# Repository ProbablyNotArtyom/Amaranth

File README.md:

https://hackaday.io/project/166535-amaranth-powerpc-homebrew-computer

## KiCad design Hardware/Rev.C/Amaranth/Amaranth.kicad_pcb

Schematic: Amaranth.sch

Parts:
C1, C2, C3, C4, C5, C6, C7, C9, C10, C11, C12, C13: 100nf; C_ARRAY_0612
C15, C16: 10pf; C_0603_1608Metric_Pad1.05x0.95mm_HandSolder
C17, C18, C19, C31, C32, C33: 100uF; CP_Elec_6.3x5.4
C20: 10nf; C_0603_1608Metric_Pad1.05x0.95mm_HandSolder
C21: 100nf; C_0603_1608Metric_Pad1.05x0.95mm_HandSolder
C22: 10uF; CP_EIA-3216-18_Kemet-A_Pad1.58x1.35mm_HandSolder
D1: LED; LED_D5.0mm
H1, H2, H3, H4: MountingHole_Pad; atx_mounting_hole
J1: RJ45_LED; RJ45_Amphenol_RJHSE538X
J2: IDE; IDC-Header_2x20_P2.54mm_Vertical
J3: ATX24; Molex_Mini-Fit_Jr_5566-24A_2x12_P4.20mm_Vertical
J4: KBD; PS2
J5: VGA; Dsub-VGA
L1: L; L_0603_1608Metric_Pad1.05x0.95mm_HandSolder
P1: JTAG; PinHeader_2x10_P2.54mm_Vertical
R1, R16, R21: 10k; R_0805_2012Metric_Pad1.15x1.40mm_HandSolder
R4: 12.4k; R_0603_1608Metric_Pad1.05x0.95mm_HandSolder
R5, R6: 330; R_0603_1608Metric_Pad1.05x0.95mm_HandSolder
R7, R8, R9, R24: 49k9; R_0603_1608Metric_Pad1.05x0.95mm_HandSolder
R10: 330; R_0805_2012Metric_Pad1.15x1.40mm_HandSolder
R11, R12: 2k; R_0805_2012Metric_Pad1.15x1.40mm_HandSolder
R13, R14: 270; R_0805_2012Metric_Pad1.15x1.40mm_HandSolder
R25: 10k; R_1206_3216Metric_Pad1.42x1.75mm_HandSolder
R26: 10k; C_0603_SMALL_REF
R27, R28, R29: 75; C_0603_SMALL_REF
R30, R33: 544; C_0603_SMALL_REF
R31, R34: 1.2k; C_0603_SMALL_REF
R32, R35: 2.4k; C_0603_SMALL_REF
R36: 455; C_0603_SMALL_REF
R37: 986; C_0603_SMALL_REF
RN1, RN2, RN3: 10k; R_ARRAY_BUSSED_8x1206
SW1: SW_SPDT; SW_Lever_1P2T_NKK_GW12LxH
U1: MCF5208; LQFP-160_24x24mm_P0.5mm
U2, U3: AS4C16M16SA; TSSOP-54_6.1x14mm_Pitch0.5mm
U4, U5, U9, U10: IS61WV25616; TSOP-II-44_10.16x18.41mm_P0.8mm
U6, U7, U20: 74LVC16245A; TSSOP-48_6.1x12.5mm_P0.5mm
U12, U14: 10M04SCE144; EQFP-144-1EP_20x20mm_P0.5mm_EP5x5mm
U13: ENC624J600-I_PT; TQFP-64_10x10mm_P0.5mm
U18: SST39SF040; PLCC-32_TH
Y1: 25MHz; Crystal_SMD_HC49-SD
Y2: 100MHz; Oscillator_SMD_EuroQuartz_XO91-4Pin_7.0x5.0mm_HandSoldering

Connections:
8b_L0: U6.48 (1LE), U12.50 (IO3/DIFFIO_TX_RX_B9n/DIFFOUT_B9n)
8b_L1: U6.25 (2LE), U12.52 (IO3/DIFFIO_TX_RX_B9p/DIFFOUT_B9p)
8b_L2: U7.48 (1LE), U12.54 (IO3)
8b_L3: U7.25 (2LE), U12.55 (IO3/DIFFIO_TX_RX_B12n/DIFFOUT_B12n)
8b_OUT: U6.1 (~1OE), U6.24 (~2OE), U7.1 (~1OE), U7.24 (~2OE), U12.56 (IO3/DIFFIO_TX_RX_B12p/DIFFOUT_B12p)
8burst_0: U12.10 (IO1A/DIFFIO_RX_L3p/DIFFOUT_L3p), U18.12 (A0)
8burst_1: U12.11 (IO1A/DIFFIO_RX_L5n/DIFFOUT_L5n), U18.11 (A1)
+1V2: U1.36 (IVDD), U1.74 (IVDD), U1.92 (IVDD), U1.94 (PLL_VDD), U1.121 (IVDD), U1.159 (IVDD)
+3V3: C1.5, C1.6, C1.7, C1.8, C2.5, C2.6, C2.7, C2.8, C3.5, C3.6, C3.7, C3.8, C4.5, C4.6, C4.7, C4.8, C5.5, C5.6, C5.7, C5.8, C6.5, C6.6, C6.7, C6.8, C7.5, C7.6, C7.7, C7.8, C9.5, C9.6, C9.7, C9.8, C10.5, C10.6, C10.7, C10.8, C11.5, C11.6, C11.7, C11.8, C12.5, C12.6, C12.7, C12.8, C13.5, C13.6, C13.7, C13.8, C17.1, C18.1, C19.1, C31.1, C32.1, C33.1, D1.2 (A), J3.1 (3V3), J3.2 (3V3), J3.12 (3V3), J3.13 (3V3), L1.2, R1.1, R16.1, R21.1, RN1.1 (common), RN2.1 (common), RN3.1 (common), U1.2 (EVDD), U1.9 (EVDD), U1.11 (SD_VDD), U1.39 (SD_VDD), U1.41 (SD_VDD), U1.67 (SD_VDD), U1.69 (EVDD), U1.72 (EVDD), U1.80 (EVDD), U1.87 (DRAMSEL), U1.89 (EVDD), U1.95 (EVDD), U1.97 (SD_VDD), U1.118 (SD_VDD), U1.129 (SD_VDD), U1.131 (EVDD), U2.1 (VDD), U2.3 (VDDQ), U2.9 (VDDQ), U2.14 (VDD), U2.27 (VDD), U2.43 (VDDQ), U2.49 (VDDQ), U3.1 (VDD), U3.3 (VDDQ), U3.9 (VDDQ), U3.14 (VDD), U3.27 (VDD), U3.43 (VDDQ), U3.49 (VDDQ), U4.11 (VCC), U4.33 (VCC), U5.11 (VCC), U5.33 (VCC), U6.7 (VCC-1), U6.18 (VCC-2), U6.31 (VCC-3), U6.42 (VCC), U7.7 (VCC-1), U7.18 (VCC-2), U7.31 (VCC-3), U7.42 (VCC), U9.11 (VCC), U9.33 (VCC), U10.11 (VCC), U10.33 (VCC), U12.1 (VCC_ONE), U12.2 (VCCA6), U12.5 (VCCA3), U12.9 (VCCIO1A), U12.23 (VCCIO1B), U12.31 (VCCIO2), U12.34 (VCCA2), U12.35 (VCCA1), U12.36 (VCC_ONE), U12.37 (VCC_ONE), U12.40 (VCCIO3), U12.49 (VCCIO3), U12.51 (VCC_ONE), U12.67 (VCCIO4), U12.71 (VCCA5), U12.72 (VCC_ONE), U12.73 (VCC_ONE), U12.82 (VCCIO5), U12.94 (VCCIO6), U12.103 (VCCIO6), U12.107 (VCCA3), U12.108 (VCC_ONE), U12.109 (VCC_ONE), U12.115 (VCC_ONE), U12.117 (VCCIO7), U12.128 (VCCIO8), U12.139 (VCCIO8), U12.143 (VCCA4), U12.144 (VCC_ONE), U13.4 (VDDOSC), U13.17 (PSPCFG2), U13.21 (VDD_2), U13.22 (VDDPLL), U13.25 (VDDRX), U13.28 (VDDTX), U13.47 (VDD_3), U13.64 (VDD), U14.1 (VCC_ONE), U14.2 (VCCA6), U14.5 (VCCA3), U14.9 (VCCIO1A), U14.23 (VCCIO1B), U14.31 (VCCIO2), U14.34 (VCCA2), U14.35 (VCCA1), U14.36 (VCC_ONE), U14.37 (VCC_ONE), U14.40 (VCCIO3), U14.49 (VCCIO3), U14.51 (VCC_ONE), U14.67 (VCCIO4), U14.71 (VCCA5), U14.72 (VCC_ONE), U14.73 (VCC_ONE), U14.82 (VCCIO5), U14.94 (VCCIO6), U14.103 (VCCIO6), U14.107 (VCCA3), U14.108 (VCC_ONE), U14.109 (VCC_ONE), U14.115 (VCC_ONE), U14.117 (VCCIO7), U14.128 (VCCIO8), U14.139 (VCCIO8), U14.143 (VCCA4), U14.144 (VCC_ONE), U18.32 (VCC), U20.7 (VCC-1), U20.18 (VCC-2), U20.31 (VCC-3), U20.42 (VCC)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
+5V: J2.29, J3.4 (5V), J3.6 (5V), J3.21 (5V), J3.22 (5V), J3.23 (5V), J4.4 (VCC), R11.1, R12.1
-5V: J3.20 (-5V)
-12V: J3.10 (12V), J3.11 (12V), J3.14 (-12)
/A0: RN1.9 (R8), U1.99 (A0), U2.23 (A0), U3.23 (A0), U12.38 (IO3/DIFFIO_TX_RX_B1n/DIFFOUT_B1n), U14.69 (IO4/DIFFIO_TX_RX_B27n/DIFFOUT_B27n)
/A1: RN1.8 (R7), U1.100 (A1), U2.24 (A1), U3.24 (A1), U12.39 (IO3/DIFFIO_TX_RX_B1p/DIFFOUT_B1p), U14.66 (IO4)
/A2: RN1.6 (R5), U1.101 (A2), U2.25 (A2), U3.25 (A2), U4.1 (A0), U5.1 (A0), U9.1 (A0), U10.1 (A0), U12.41 (IO3/DIFFIO_TX_RX_B3n/DIFFOUT_B3n), U14.65 (IO4/DIFFIO_TX_RX_B23p/DIFFOUT_B23p), U18.10 (A2)
/A3: RN1.5 (R4), U1.102 (A3), U2.26 (A3), U3.26 (A3), U4.2 (A1), U5.2 (A1), U9.2 (A1), U10.2 (A1), U12.43 (IO3/DIFFIO_TX_RX_B3p/DIFFOUT_B3p), U14.64 (IO4/DIFFIO_TX_RX_B23n/DIFFOUT_B23n), U18.9 (A3)
/A4: RN1.4 (R3), U1.103 (A4), U2.29 (A4), U3.29 (A4), U4.3 (A2), U5.3 (A2), U9.3 (A2), U10.3 (A2), U12.44 (IO3/DIFFIO_TX_RX_B5n/DIFFOUT_B5n), U13.57 (A0), U14.62 (IO4), U18.8 (A4)
/A5: RN1.3 (R2), U1.104 (A5), U2.30 (A5), U3.30 (A5), U4.4 (A3), U5.4 (A3), U9.4 (A3), U10.4 (A3), U12.45 (IO3/DIFFIO_TX_RX_B5p/DIFFOUT_B5p), U13.58 (A1), U14.61 (IO4/VREFB4N0), U18.7 (A5)
/A9: RN2.4 (R3), U1.108 (A9), U2.34 (A9), U3.34 (A9), U4.20 (A7), U5.20 (A7), U9.20 (A7), U10.20 (A7), U13.9 (A5), U14.57 (IO3/DIFFIO_TX_RX_B14n/DIFFOUT_B14n), U18.26 (A9)
/A10: RN2.3 (R2), U1.109 (A10), U4.21 (A8), U5.21 (A8), U9.21 (A8), U10.21 (A8), U13.10 (A6), U14.56 (IO3/DIFFIO_TX_RX_B12p/DIFFOUT_B12p), U18.23 (A10)
/A11: RN2.2 (R1), U1.110 (A11), U2.35 (A11), U3.35 (A11), U4.22 (A9), U5.22 (A9), U9.22 (A9), U10.22 (A9), U13.11 (A7), U14.55 (IO3/DIFFIO_TX_RX_B12n/DIFFOUT_B12n), U18.25 (A11)
/A12: RN2.6 (R5), U1.111 (A12), U2.36 (A12), U3.36 (A12), U4.23 (A10), U5.23 (A10), U9.23 (A10), U10.23 (A10), U13.12 (A8), U14.54 (IO3), U18.4 (A12)
/A13: RN2.7 (R6), U1.112 (A13), U4.24 (A11), U5.24 (A11), U9.24 (A11), U10.24 (A11), U13.13 (A9), U14.52 (IO3/DIFFIO_TX_RX_B9p/DIFFOUT_B9p), U18.28 (A13)
/A14: RN2.8 (R7), U1.113 (A14), U2.20 (BA0), U3.20 (BA0), U4.25 (A12), U5.25 (A12), U9.25 (A12), U10.25 (A12), U13.19 (A10), U14.50 (IO3/DIFFIO_TX_RX_B9n/DIFFOUT_B9n), U18.29 (A14)
/A15: RN2.9 (R8), U1.114 (A15), U2.21 (BA1), U3.21 (BA1), U4.26 (A13), U5.26 (A13), U9.26 (A13), U10.26 (A13), U13.20 (A11), U14.48 (IO3/VREFB3N0), U18.3 (A15)
/A16: RN3.9 (R8), U1.115 (A16), U4.27 (A14), U5.27 (A14), U9.27 (A14), U10.27 (A14), U13.43 (A12), U14.47 (IO3/DIFFIO_TX_RX_B7p/DIFFOUT_B7p), U18.2 (A16)
/A17: RN3.2 (R1), U1.116 (A17), U4.42 (A15), U5.42 (A15), U9.42 (A15), U10.42 (A15), U13.44 (A13), U14.46 (IO3/DIFFIO_TX_RX_B7n/DIFFOUT_B7n), U18.30 (A17)
/A18: RN3.8 (R7), U1.120 (A18), U4.43 (A16), U5.43 (A16), U9.43 (A16), U10.43 (A16), U13.45 (A14/PSPCFG1), U14.45 (IO3/DIFFIO_TX_RX_B5p/DIFFOUT_B5p), U18.1 (A18)
/A19: RN3.3 (R2), U1.122 (A19), U4.44 (A17), U5.44 (A17), U9.44 (A17), U10.44 (A17), U14.44 (IO3/DIFFIO_TX_RX_B5n/DIFFOUT_B5n)
/A20: RN3.7 (R6), U1.123 (A20), U14.43 (IO3/DIFFIO_TX_RX_B3p/DIFFOUT_B3p)
/A21: RN3.4 (R3), U1.124 (A21), U14.41 (IO3/DIFFIO_TX_RX_B3n/DIFFOUT_B3n)
/A22: RN3.6 (R5), U1.125 (A22), U14.39 (IO3/DIFFIO_TX_RX_B1p/DIFFOUT_B1p)
/A23: RN3.5 (R4), U1.126 (A23), U14.38 (IO3/DIFFIO_TX_RX_B1n/DIFFOUT_B1n)
/DL0: U1.27 (D31), U2.2 (DQ0), U5.7 (D0), U6.47 (1D1), U9.7 (D0), U13.53 (AD0), U14.120 (IO8/DIFFIO_RX_T16p/DIFFOUT_T16p), U20.22 (2B7)
/DL1: U1.28 (D30), U2.4 (DQ1), U5.8 (D1), U6.46 (1D2), U9.8 (D1), U13.54 (AD1), U14.121 (IO8/DIFFIO_RX_T16n/DIFFOUT_T16n/DEV_CLRn), U20.19 (2B5)
/DL2: U1.29 (D29), U2.5 (DQ2), U5.9 (D2), U6.44 (1D3), U9.9 (D2), U13.55 (AD2), U14.122 (IO8/DEV_OE), U20.16 (2B3)
/DL3: U1.30 (D28), U2.7 (DQ3), U5.10 (D3), U6.43 (1D4), U9.10 (D3), U13.56 (AD3), U14.123 (IO8/VREFB8N0), U20.13 (2B1)
/DL4: U1.31 (D27), U2.8 (DQ4), U5.13 (D4), U6.41 (1D5), U9.13 (D4), U13.5 (AD4), U14.126 (IO8/CONFIG_SEL), U20.11 (1B7)
/DL5: U1.32 (D26), U2.10 (DQ5), U5.14 (D5), U6.40 (1D6), U9.14 (D5), U13.6 (AD5), U14.124 (IO8/DIFFIO_RX_T19p/DIFFOUT_T19p), U20.8 (1B5)
/DL6: U1.33 (D25), U2.11 (DQ6), U5.15 (D6), U6.38 (1D7), U9.15 (D6), U13.7 (AD6), U14.129 (IN8/nCONFIG), U20.5 (1B3)
/DL7: U1.34 (D24), U2.13 (DQ7), U5.16 (D7), U6.37 (1D8), U9.16 (D7), U13.8 (AD7), U14.127 (IO8/DIFFIO_RX_T19n/DIFFOUT_T19n), U20.2 (1B1)
/DL8: U1.46 (D23), U2.42 (DQ8), U5.29 (D8), U6.36 (2D1), U9.29 (D8), U13.35 (AD8), U20.3 (1B2)
/DL9: U1.47 (D22), U2.44 (DQ9), U5.30 (D9), U6.35 (2D2), U9.30 (D9), U13.36 (AD9), U20.6 (1B4)
/DL10: U1.48 (D21), U2.45 (DQ10), U5.31 (D10), U6.33 (2D3), U9.31 (D10), U13.37 (AD10), U20.9 (1B6)
/DL11: U1.49 (D20), U2.47 (DQ11), U5.32 (D11), U6.32 (2D4), U9.32 (D11), U13.38 (AD11), U20.12 (1B8)
/DL12: U1.50 (D19), U2.48 (DQ12), U5.35 (D12), U6.30 (2D5), U9.35 (D12), U13.39 (AD12), U20.14 (2B2)
/DL13: U1.51 (D18), U2.50 (DQ13), U5.36 (D13), U6.29 (2D6), U9.36 (D13), U13.40 (AD13), U20.17 (2B4)
/DL14: U1.52 (D17), U2.51 (DQ14), U5.37 (D14), U6.27 (2D7), U9.37 (D14), U13.41 (AD14), U20.20 (2B6)
/DL15: U1.53 (D16), U2.53 (DQ15), U5.38 (D15), U6.26 (2D8), U9.38 (D15), U13.42 (AD15), U20.23 (2B8)
/DL16: U1.16 (D15), U3.2 (DQ0), U4.7 (D0), U7.47 (1D1), U10.7 (D0)
/DL17: U1.17 (D14), U3.4 (DQ1), U4.8 (D1), U7.46 (1D2), U10.8 (D1)
/DL18: U1.18 (D13), U3.5 (DQ2), U4.9 (D2), U7.44 (1D3), U10.9 (D2)
/DL19: U1.19 (D12), U3.7 (DQ3), U4.10 (D3), U7.43 (1D4), U10.10 (D3)
/DL20: U1.20 (D11), U3.8 (DQ4), U4.13 (D4), U7.41 (1D5), U10.13 (D4)
/DL21: U1.21 (D10), U3.10 (DQ5), U4.14 (D5), U7.40 (1D6), U10.14 (D5)
/DL22: U1.22 (D9), U3.11 (DQ6), U4.15 (D6), U7.38 (1D7), U10.15 (D6)
/DL23: U1.23 (D8), U3.13 (DQ7), U4.16 (D7), U7.37 (1D8), U10.16 (D7)
/DL24: U1.57 (D7), U3.42 (DQ8), U4.29 (D8), U7.36 (2D1), U10.29 (D8)
/DL25: U1.58 (D6), U3.44 (DQ9), U4.30 (D9), U7.35 (2D2), U10.30 (D9)
/DL26: U1.59 (D5), U3.45 (DQ10), U4.31 (D10), U7.33 (2D3), U10.31 (D10)
/DL27: U1.60 (D4), U3.47 (DQ11), U4.32 (D11), U7.32 (2D4), U10.32 (D11)
/DL28: U1.61 (D3), U3.48 (DQ12), U4.35 (D12), U7.30 (2D5), U10.35 (D12)
/DL29: U1.62 (D2), U3.50 (DQ13), U4.36 (D13), U7.29 (2D6), U10.36 (D13)
/DL30: U1.63 (D1), U3.51 (DQ14), U4.37 (D14), U7.27 (2D7), U10.37 (D14)
/DL31: U1.64 (D0), U3.53 (DQ15), U4.38 (D15), U7.26 (2D8), U10.38 (D15)
/DR0: U6.2 (1Q1), U6.13 (2Q1), U7.2 (1Q1), U7.13 (2Q1), U18.13 (D0)
/DR1: U6.3 (1Q2), U6.14 (2Q2), U7.3 (1Q2), U7.14 (2Q2), U18.14 (D1)
/DR2: U6.5 (1Q3), U6.16 (2Q3), U7.5 (1Q3), U7.16 (2Q3), U18.15 (D2)
/DR3: U6.6 (1Q4), U6.17 (2Q4), U7.6 (1Q4), U7.17 (2Q4), U18.17 (D3)
/DR4: U6.8 (1Q5), U6.19 (2Q5), U7.8 (1Q5), U7.19 (2Q5), U18.18 (D4)
/DR5: U6.9 (1Q6), U6.20 (2Q6), U7.9 (1Q6), U7.20 (2Q6), U18.19 (D5)
/DR6: U6.11 (1Q7), U6.22 (2Q7), U7.11 (1Q7), U7.22 (2Q7), U18.20 (D6)
/DR7: U6.12 (1Q8), U6.23 (2Q8), U7.12 (1Q8), U7.23 (2Q8), U18.21 (D7)
/IDE_D0: J2.17, U20.27 (2A7)
/IDE_D1: J2.15, U20.30 (2A5)
/IDE_D2: J2.13, U20.33 (2A3)
/IDE_D3: J2.11, U20.36 (2A1)
/IDE_D4: J2.9, U20.38 (1A7)
/IDE_D5: J2.7, U20.41 (1A5)
/IDE_D6: J2.5, U20.44 (1A3)
/IDE_D7: J2.3, U20.47 (1A1)
/IDE_D8: J2.4, U20.46 (1A2)
/IDE_D9: J2.6, U20.43 (1A4)
/IDE_D10: J2.8, U20.40 (1A6)
/IDE_D11: J2.10, U20.37 (1A8)
/IDE_D12: J2.12, U20.35 (2A2)
/IDE_D13: J2.14, U20.32 (2A4)
/IDE_D14: J2.16, U20.29 (2A6)
/IDE_D15: J2.18, U20.26 (2A8)
/RXI+: J1.7, R8.2, U13.26 (TPIN+)
/RXI-: J1.8, R7.1, U13.27 (TPIN-)
/TXO+: J1.1, R9.2, U13.30 (TPOUT+)
/TXO-: J1.2, R24.1, U13.31 (TPOUT-)
A6: J2.35, RN1.2 (R1), U1.105 (A6), U2.31 (A6), U3.31 (A6), U4.5 (A4), U5.5 (A4), U9.5 (A4), U10.5 (A4), U12.46 (IO3/DIFFIO_TX_RX_B7n/DIFFOUT_B7n), U13.59 (A2), U14.60 (IO3/DIFFIO_TX_RX_B16p/DIFFOUT_B16p), U18.6 (A6)
A7: J2.33, RN1.7 (R6), U1.106 (A7), U2.32 (A7), U3.32 (A7), U4.18 (A5), U5.18 (A5), U9.18 (A5), U10.18 (A5), U12.47 (IO3/DIFFIO_TX_RX_B7p/DIFFOUT_B7p), U13.60 (A3), U14.59 (IO3/DIFFIO_TX_RX_B16n/DIFFOUT_B16n), U18.5 (A7)
A8: J2.36, RN2.5 (R4), U1.107 (A8), U2.33 (A8), U3.33 (A8), U4.19 (A6), U5.19 (A6), U9.19 (A6), U10.19 (A6), U13.61 (A4), U14.58 (IO3/DIFFIO_TX_RX_B14p/DIFFOUT_B14p), U18.27 (A8)
AP0: U12.75 (IO5/DIFFIO_RX_R1p/DIFFOUT_R1p)
AP1: U12.77 (IO5/DIFFIO_RX_R1n/DIFFOUT_R1n)
AP2: U12.74 (IO5/DIFFIO_RX_R2p/DIFFOUT_R2p)
AP3: U12.76 (IO5/DIFFIO_RX_R2n/DIFFOUT_R2n)
APE: U12.79 (IO5/DIFFIO_RX_R7p/DIFFOUT_R7p)
BWE0: U1.56 (~BE/BWE0), U2.15 (DQML), U5.39 (~LB), U9.39 (~LB)
BWE1: U1.24 (~BE/BWE1), U2.39 (DQMH), U5.40 (~UB), U9.40 (~UB)
BWE2: U1.54 (~BE/BWE2), U3.15 (DQML), U4.39 (~LB), U10.39 (~LB)
BWE3: U1.26 (~BE/BWE3), U3.39 (DQMH), U4.40 (~UB), U10.40 (~UB)
CS_ETH: U12.130 (IO8/DIFFIO_RX_T20p/DIFFOUT_T20p), U13.49 (~CS/CS)
CS_ROM: U12.136 (IO8/DIFFIO_RX_T24p/DIFFOUT_T24p/nSTATUS), U18.22 (CE)
CS_SDRAM: U12.122 (IO8/DEV_OE)
CS_SRAM_0: U9.6 (~CE), U12.131 (IO8/DIFFIO_RX_T20n/DIFFOUT_T20n)
CS_SRAM_1: U10.6 (~CE), U12.132 (IO8/DIFFIO_RX_T22p/DIFFOUT_T22p)
CS_SRAM_2: U5.6 (~CE), U12.134 (IO8/DIFFIO_RX_T22n/DIFFOUT_T22n/CRC_ERR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)
CS_SRAM_3: U4.6 (~CE), U12.135 (IO8)
CS_VGAMEM: U12.123 (IO8/VREFB8N0), U14.7 (IO1A/DIFFIO_RX_L1p/DIFFOUT_L1p)
DPE: U12.78 (IO5)
DQM0: U13.50 (SO/WR/WRL/EN/BOSEL)
DQM1: U13.48 (WRH/B1SEL)
GND: C1.1, C1.2, C1.3, C1.4, C2.1, C2.2, C2.3, C2.4, C3.1, C3.2, C3.3, C3.4, C4.1, C4.2, C4.3, C4.4, C5.1, C5.2, C5.3, C5.4, C6.1, C6.2, C6.3, C6.4, C7.1, C7.2, C7.3, C7.4, C9.1, C9.2, C9.3, C9.4, C10.1, C10.2, C10.3, C10.4, C11.1, C11.2, C11.3, C11.4, C12.1, C12.2, C12.3, C12.4, C13.1, C13.2, C13.3, C13.4, C15.2, C16.2, C17.2, C18.2, C19.2, C20.2, C21.2, C22.2, C31.2, C32.2, C33.2, H1.1, H2.1, H3.1, H4.1, J1.4, J1.5, J2.2, J2.19, J2.22, J2.24, J2.26, J2.30, J2.40, J3.3 (GND), J3.5 (GND), J3.7 (GND), J3.15 (GND), J3.17 (GND), J3.18 (GND), J3.19 (GND), J3.24 (GND), J4.3 (GND), J5.0, J5.5, J5.6, J5.7, J5.8, J5.10, P1.4 (GND), P1.6 (GND), P1.8 (GND), P1.10 (GND), P1.11 (RTCK), P1.12 (GND), P1.14 (GND), P1.16 (GND), P1.18 (GND), P1.20 (GND), R4.1, R5.1, R6.1, R10.2, R25.1, R26.2, R27.2, R28.2, R29.2, SW1.3 (C), U1.1 (VSS), U1.10 (VSS), U1.42 (VSS), U1.68 (VSS), U1.71 (VSS), U1.81 (VSS), U1.93 (PLL_VSS), U1.96 (VSS), U1.117 (VSS), U1.119 (VSS), U1.130 (VSS), U2.6 (VSSQ), U2.12 (VSSQ), U2.28 (VSS), U2.41 (VSS), U2.46 (VSSQ), U2.52 (VSSQ), U2.54 (VSS), U3.6 (VSSQ), U3.12 (VSSQ), U3.28 (VSS), U3.41 (VSS), U3.46 (VSSQ), U3.52 (VSSQ), U3.54 (VSS), U4.12 (GND), U4.34 (GND), U5.12 (GND), U5.34 (GND), U6.4 (GND-3), U6.10 (GND-4), U6.15 (GND-5), U6.21 (GND), U6.28 (GND-1), U6.34 (GND-7), U6.39 (GND-6), U6.45 (GND-2), U7.4 (GND-3), U7.10 (GND-4), U7.15 (GND-5), U7.21 (GND), U7.28 (GND-1), U7.34 (GND-7), U7.39 (GND-6), U7.45 (GND-2), U9.12 (GND), U9.34 (GND), U10.12 (GND), U10.34 (GND), U12.3 (GND), U12.4 (GND), U12.42 (GND), U12.53 (GND), U12.63 (GND), U12.68 (GND), U12.83 (GND), U12.95 (GND), U12.104 (GND), U12.116 (GND), U12.125 (GND), U12.133 (GND), U12.137 (GND), U12.142 (GND), U12.145 (GND), U13.1 (VSSOSC), U13.18 (PSPCFG3), U13.23 (VSSPLL), U13.24 (VSSRX), U13.29 (VSSTX1), U13.32 (VSSTX), U13.46 (VSS_2), U13.52 (SCK/AL/PSPCFG4), U13.62 (VSS), U14.3 (GND), U14.4 (GND), U14.42 (GND)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
HSYNC: J5.13, U14.88 (IO6/DIFFIO_RX_R14p/DIFFOUT_R14p/CLK2p)
IDE_0: J2.37, U12.129 (IN8/nCONFIG)
IDE_1: J2.38, U12.127 (IO8/DIFFIO_RX_T19n/DIFFOUT_T19n)
IDE_DIR: U12.124 (IO8/DIFFIO_RX_T19p/DIFFOUT_T19p), U20.1 (1DIR), U20.24 (2DIR)
IDE_OE: U12.126 (IO8/CONFIG_SEL), U20.25 (2OE), U20.48 (1OE)
INT: U12.110 (IO7/DIFFIO_RX_T1p/DIFFOUT_T1p)
INT_ETH: R26.1, U12.90 (IO6/DIFFIO_RX_R16p/DIFFOUT_R16p/CLK3p), U13.34 (~INT/SPISEL)
JT_CHAIN0: U1.75 (TDO/DSO), U12.19 (IO1B/DIFFIO_RX_L12n/DIFFOUT_L12n/TDI)
JT_CHAIN1: U12.20 (IO1B/DIFFIO_RX_L12p/DIFFOUT_L12p/TDO), U14.19 (IO1B/DIFFIO_RX_L12n/DIFFOUT_L12n/TDI)
JT_CHAIN2: P1.13 (TDO), U14.20 (IO1B/DIFFIO_RX_L12p/DIFFOUT_L12p/TDO)
JT_TCK: P1.9 (TCK), U1.70 (TCLK/PSTCLK), U12.18 (IO1B/DIFFIO_RX_L11p/DIFFOUT_L11p/TCK), U14.18 (IO1B/DIFFIO_RX_L11p/DIFFOUT_L11p/TCK)
JT_TDI: P1.5 (TDI), U1.85 (TDI/DSI)
JT_TMS: P1.7 (TMS), U1.83 (TMS/BKPT), U12.16 (IO1B/DIFFIO_RX_L11n/DIFFOUT_L11n/TMS), U14.16 (IO1B/DIFFIO_RX_L11n/DIFFOUT_L11n/TMS)
unnamed: C15.1, U13.3 (OSC1), Y1.1
unnamed: C16.1, U13.2 (OSC2), Y1.2
unnamed: C20.1, R7.2, R8.1
unnamed: C21.1, J1.3, L1.1, R9.1, R24.2
unnamed: C22.1, U13.63 (VCAP)
unnamed: D1.1 (K), R10.1
unnamed: J1.9, U13.14 (LEDB)
unnamed: J1.10, R6.2
unnamed: J1.11, U13.15 (LEDA)
unnamed: J1.12, R5.2
unnamed: J2.31, R25.2
unnamed: J3.9 (5VSB), SW1.1 (A)
unnamed: J3.16 (PS_ON), SW1.2 (B)
unnamed: J4.1 (DATA), R14.2
unnamed: J4.5 (CLK), R13.2
unnamed: J5.1, R27.1, R30.1, R31.1, R32.1
unnamed: J5.2, R28.1, R33.1, R34.1, R35.1
unnamed: J5.3, R29.1, R36.1, R37.1
unnamed: P1.3 (~TRST), U1.84 (TRST/DSCLK)
unnamed: R1.2, U1.140 (IRQ1)
unnamed: R4.2, U13.16 (RBIAS)
unnamed: R11.2, R14.1, U12.89 (IO6/DIFFIO_RX_R14n/DIFFOUT_R14n/CLK2n)
unnamed: R12.2, R13.1, U12.88 (IO6/DIFFIO_RX_R14p/DIFFOUT_R14p/CLK2p)
unnamed: R16.2, U1.141 (IRQ4)
unnamed: R21.2, U1.142 (IRQ7)
unnamed: R30.2, U14.75 (IO5/DIFFIO_RX_R1p/DIFFOUT_R1p)
unnamed: R31.2, U14.77 (IO5/DIFFIO_RX_R1n/DIFFOUT_R1n)
unnamed: R32.2, U14.74 (IO5/DIFFIO_RX_R2p/DIFFOUT_R2p)
unnamed: R33.2, U14.76 (IO5/DIFFIO_RX_R2n/DIFFOUT_R2n)
unnamed: R34.2, U14.79 (IO5/DIFFIO_RX_R7p/DIFFOUT_R7p)
unnamed: R35.2, U14.78 (IO5)
unnamed: R36.2, U14.81 (IO5/DIFFIO_RX_R7n/DIFFOUT_R7n)
unnamed: R37.2, U14.80 (IO5/VREFB5N0)
unnamed: U1.25 (SD_DQS3), U1.35 (SD_SDR_DQS), U1.55 (SD_DQS2)
unnamed: U14.26 (IO2/DIFFIO_RX_L18n/DIFFOUT_L18n/CLK0n), Y2.3 (OUT)
READ: J2.25, U4.41 (~OE), U5.41 (~OE), U9.41 (~OE), U10.41 (~OE), U12.120 (IO8/DIFFIO_RX_T16p/DIFFOUT_T16p), U13.51 (SI/RD/R~W), U18.24 (OE)
RESET: J2.1
SD_A10: U1.43 (SD_A10), U2.22 (A10), U3.22 (A10)
SD_CAS: U1.44 (~SD_CAS), U2.17 (~CAS~), U3.17 (~CAS~)
SD_CKE: U1.14 (SD_CKE), U2.37 (CKE), U3.37 (CKE)
SD_CLK: U1.37 (SD_CLK), U2.38 (CLK), U3.38 (CLK)
SD_CS: U1.15 (~SD_CS), U2.19 (~CS~), U3.19 (~CS~)
SD_DDIR: U14.32 (IO2/DIFFIO_RX_L27n/DIFFOUT_L27n/PLL_L_C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)
SD_DOE: U14.33 (IO2/DIFFIO_RX_L27p/DIFFOUT_L27p/PLL_L_C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)
SD_RAS: U1.45 (~SD_RAS), U2.18 (~RAS~), U3.18 (~RAS~)
SD_WE: U1.13 (~SD_WE), U2.16 (~WE~), U3.16 (~WE~)
SRESET: P1.15 (~SRST)
SYSCLK: U14.90 (IO6/DIFFIO_RX_R16p/DIFFOUT_R16p/CLK3p)
TLBISYNC: U12.111 (IO7/DIFFIO_RX_T1n/DIFFOUT_T1n)
TSIZ0: U12.81 (IO5/DIFFIO_RX_R7n/DIFFOUT_R7n)
TSIZ1: U12.80 (IO5/VREFB5N0)
TSIZ2: U12.85 (IO5/DIFFIO_RX_R10p/DIFFOUT_R10p)
TT0: U12.101 (IO6/DIFFIO_RX_R27n/DIFFOUT_R27n)
TT1: U12.100 (IO6/DIFFIO_RX_R28p/DIFFOUT_R28p)
TT2: U12.102 (IO6/DIFFIO_RX_R28n/DIFFOUT_R28n)
TT3: U12.105 (IO6/DIFFIO_RX_R33p/DIFFOUT_R33p)
TT4: U12.106 (IO6/DIFFIO_RX_R33n/DIFFOUT_R33n)
VSYNC: J5.14, U14.89 (IO6/DIFFIO_RX_R14n/DIFFOUT_R14n/CLK2n)
WRITE: J2.23, U4.17 (~WE), U5.17 (~WE), U9.17 (~WE), U10.17 (~WE), U12.121 (IO8/DIFFIO_RX_T16n/DIFFOUT_T16n/DEV_CLRn), U18.31 (PGM)

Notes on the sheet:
Peripherals

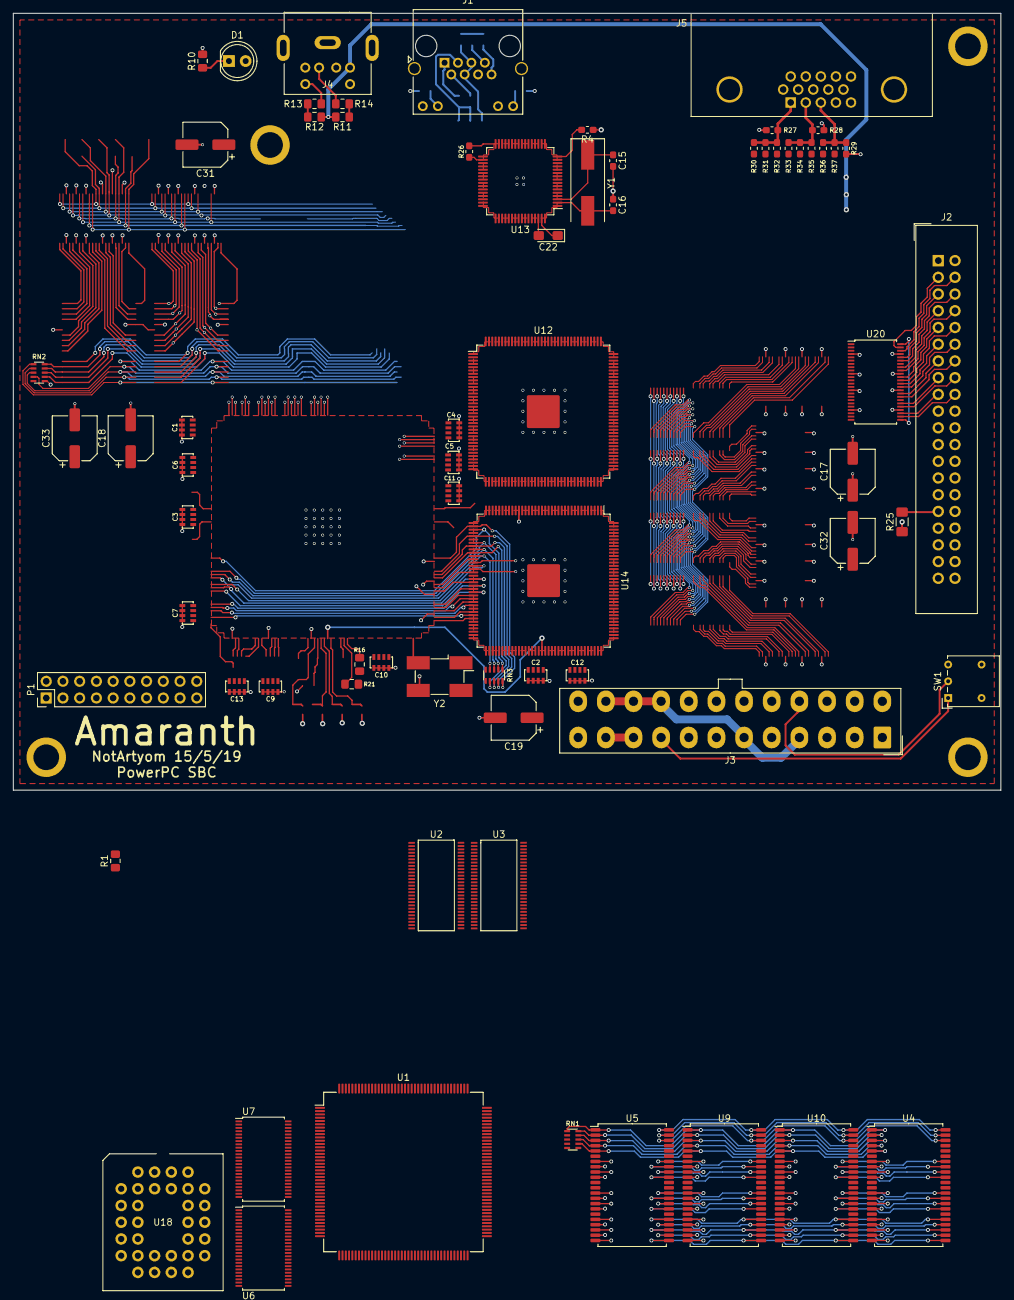
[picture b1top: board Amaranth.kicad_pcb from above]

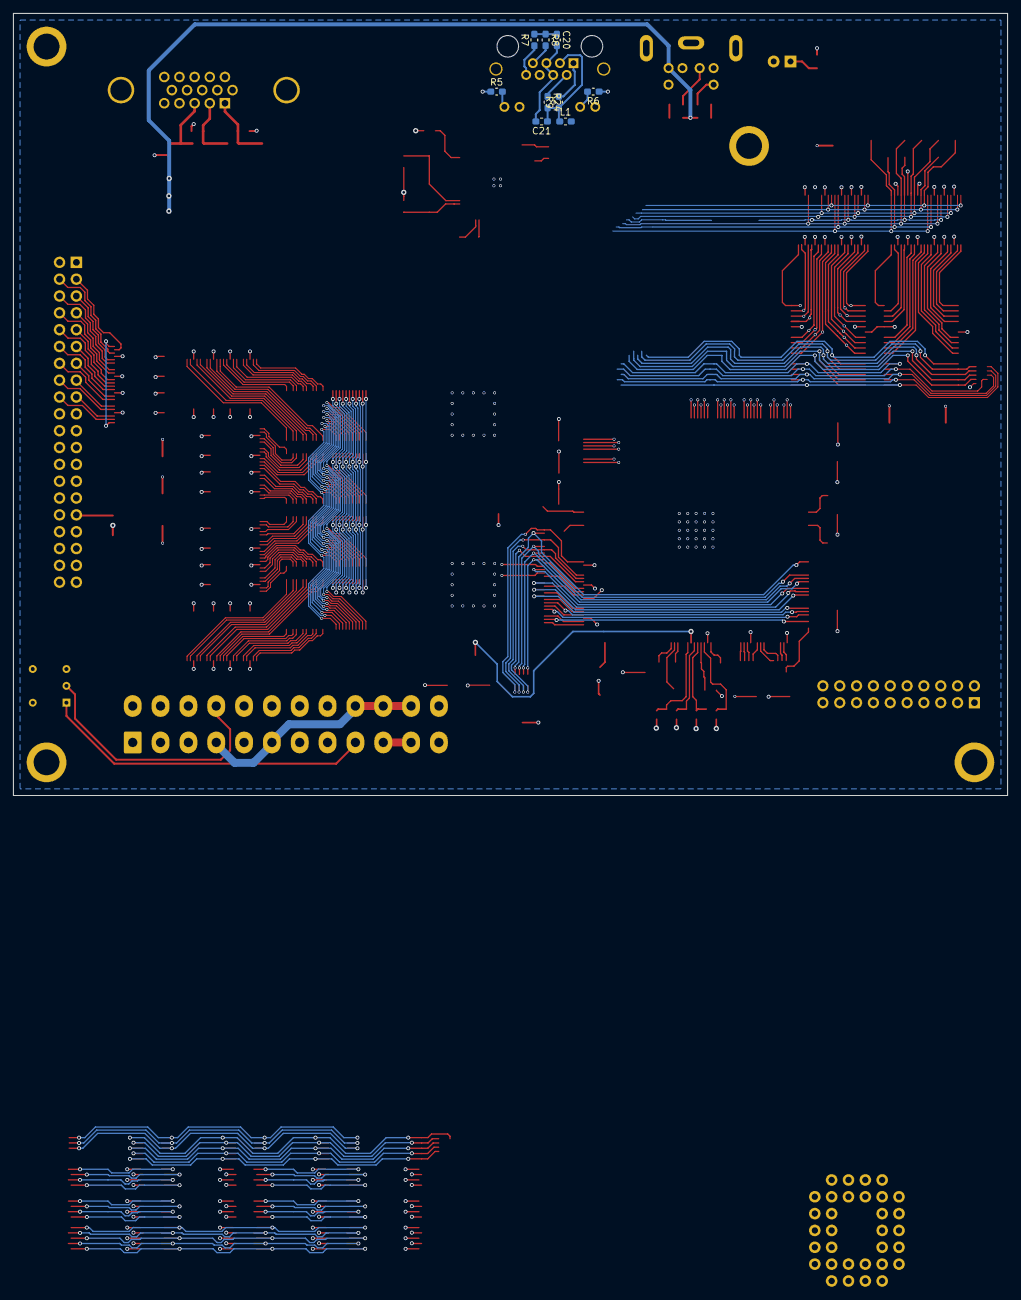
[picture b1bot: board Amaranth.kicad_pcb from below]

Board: 4 copper layers, 150.0 x 118.0 mm, 83 parts (9 on the bottom side), 164 nets.

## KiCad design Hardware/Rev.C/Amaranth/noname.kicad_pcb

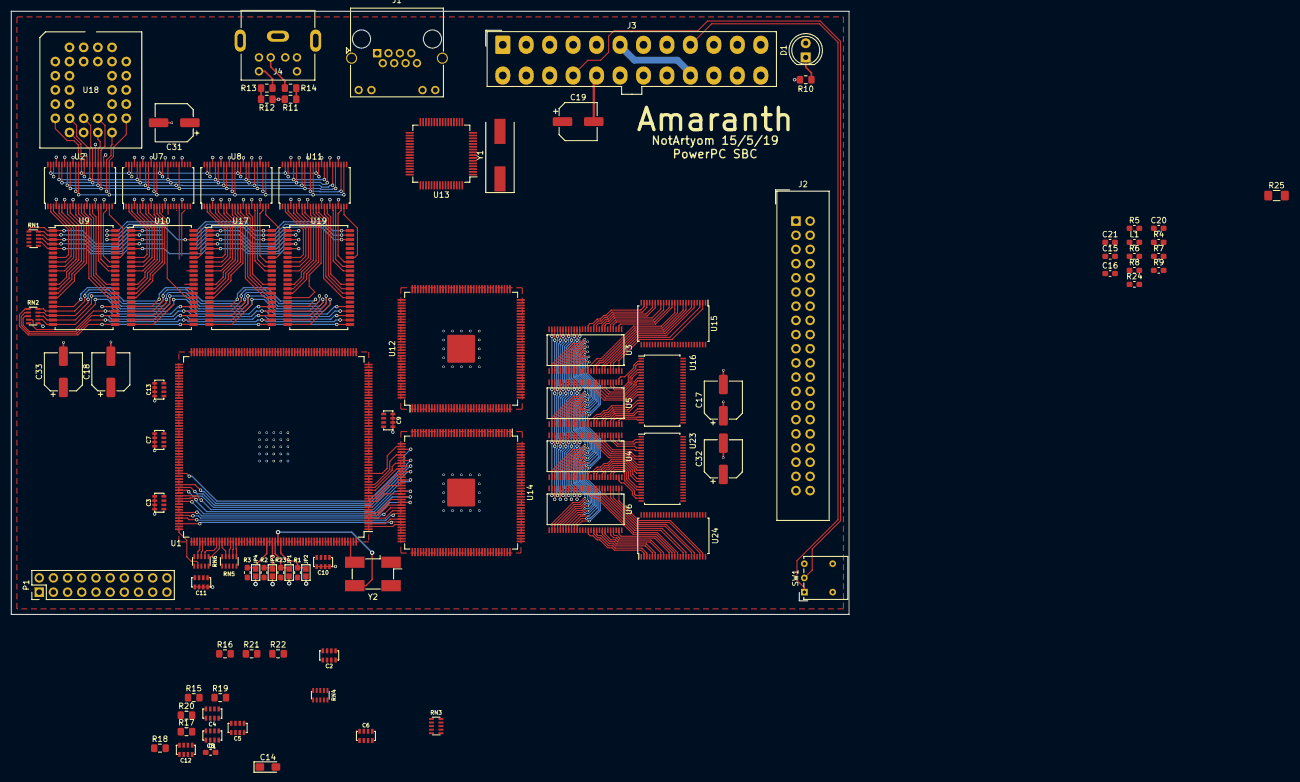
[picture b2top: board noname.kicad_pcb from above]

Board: 4 copper layers, 150.0 x 108.0 mm, 90 parts (0 on the bottom side), 273 nets.

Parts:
C1, C2, C3, C4, C5, C6, C7, C9, C10, C11, C12, C13: 100nf; C_ARRAY_0612
C8: 100nf; C_0603_SMALL_REF
C14: 10uF; CP_EIA-3216-18_Kemet-A_Pad1.58x1.35mm_HandSolder
C15, C16: 10pf; C_0603_1608Metric_Pad1.05x0.95mm_HandSolder
C17, C18, C19, C31, C32, C33: 100uF; CP_Elec_6.3x5.4
C20: 10nf; C_0603_1608Metric_Pad1.05x0.95mm_HandSolder
C21: 100nf; C_0603_1608Metric_Pad1.05x0.95mm_HandSolder
D1: LED; LED_D5.0mm
J1: RJ45_LED; RJ45_Amphenol_RJHSE538X
J2: IDE; IDC-Header_2x20_P2.54mm_Vertical
J3: ATX24; Molex_Mini-Fit_Jr_5566-24A_2x12_P4.20mm_Vertical
J4: KBD; PS2
JP1, JP2, JP3, JP4: Jumper_NO_Small; smd_jumper_small
L1: L; L_0603_1608Metric_Pad1.05x0.95mm_HandSolder
P1: JTAG; PinHeader_2x10_P2.54mm_Vertical
R1, R2, R3, R23: 10k; C_0603_SMALL_REF
R4: 12.3k; R_0603_1608Metric_Pad1.05x0.95mm_HandSolder
R5, R6: 330; R_0603_1608Metric_Pad1.05x0.95mm_HandSolder
R7, R8, R9, R24: 49k9; R_0603_1608Metric_Pad1.05x0.95mm_HandSolder
R10: 330; R_0805_2012Metric_Pad1.15x1.40mm_HandSolder
R11, R12: 2k; R_0805_2012Metric_Pad1.15x1.40mm_HandSolder
R13, R14: 270; R_0805_2012Metric_Pad1.15x1.40mm_HandSolder
R15, R16, R17, R18, R19, R20, R21, R22: 10k; R_0805_2012Metric_Pad1.15x1.40mm_HandSolder
R25: 10k; R_1206_3216Metric_Pad1.42x1.75mm_HandSolder
RN1, RN2, RN3, RN4, RN5, RN6: 10k; R_ARRAY_BUSSED_8x1206
SW1: SW_SPDT; SW_Lever_1P2T_NKK_GW12LxH
U1: PPC603e; PQFP-240_32.1x32.1mm_P0.5mm
U2, U7, U8, U11: 74LVC16373A; TSSOP-48_6.1x12.5mm_P0.5mm
U3, U4, U5, U6: AS4C16M16SA; TSSOP-54_6.1x14mm_Pitch0.5mm
U9, U10, U17, U19: IS61WV25616; TSOP-II-44_10.16x18.41mm_P0.8mm
U12, U14: 10M04SCE144; EQFP-144-1EP_20x20mm_P0.5mm_EP5x5mm
U13: ENC624J600-I_PT; TQFP-64_10x10mm_P0.5mm
U15, U16, U23, U24: 74LVC16245A; TSSOP-48_6.1x12.5mm_P0.5mm
U18: SST39SF040; PLCC-32_TH
Y1: 25MHz; Crystal_SMD_HC49-SD
Y2: 25MHz; Oscillator_SMD_EuroQuartz_XO91-4Pin_7.0x5.0mm_HandSoldering

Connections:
8b_OUT: U2.1, U2.24, U7.1, U7.24, U8.1, U8.24, U11.1, U11.24, U12.130
8burst_0: U12.10, U18.12
8burst_1: U12.11, U18.11
8burst_2: U12.12, U18.10
8burst_3: U12.13, U18.9
+3V3: C1.5, C1.6, C1.7, C1.8, C2.5, C2.6, C2.7, C2.8, C3.5, C3.6, C3.7, C3.8, C4.5, C4.6, C4.7, C4.8, C5.5, C5.6, C5.7, C5.8, C6.5, C6.6, C6.7, C6.8, C7.5, C7.6, C7.7, C7.8, C9.5, C9.6, C9.7, C9.8, C10.5, C10.6, C10.7, C10.8, C11.5, C11.6, C11.7, C11.8, C12.5, C12.6, C12.7, C12.8, C13.5, C13.6, C13.7, C13.8, C17.1, C18.1, C19.1, C31.1, C32.1, C33.1, J3.1, J3.2, J3.12, J3.13, L1.2, R1.1, R2.1, R3.1, R15.1, R16.1, R17.1, R18.1, R19.1, R20.1, R21.1, R22.1, R23.1, RN1.1, RN2.1, RN3.1, RN4.1, RN5.1, RN6.1, U1.4, U1.10, U1.14, U1.20, U1.24, U1.34, U1.35, U1.44, U1.45, U1.54, U1.59, U1.61, U1.70, U1.79, U1.88, U1.96, U1.104, U1.112, U1.121, U1.122, U1.128, U1.137, U1.138, U1.147, U1.148, U1.157, U1.163, U1.167, U1.173, U1.177, U1.183, U1.194, U1.205, U1.207, U1.222, U1.229, U1.240, U2.7, U2.18, U2.31, U2.42, U3.1, U3.3, U3.9, U3.14, U3.27, U3.43, U3.49, U4.1, U4.3, U4.9, U4.14, U4.27, U4.43, U4.49, U5.1, U5.3, U5.9, U5.14, U5.27, U5.43, U5.49, U6.1, U6.3, U6.9, U6.14, U6.27, U6.43, U6.49, U7.7, U7.18, U7.31, U7.42, U8.7, U8.18, U8.31, U8.42, U9.11, U9.33, U10.11, U10.33, U11.7, U11.18, U11.31, U11.42, U12.1, U12.2, U12.5, U12.9, U12.23, U12.31, U12.34, U12.35, U12.36, U12.37, U12.40, U12.49, U12.51, U12.67, U12.71, U12.72, U12.73, U12.82, U12.94, U12.103, U12.107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
+5V: D1.2, J2.29, J2.38, J3.4, J3.6, J3.21, J3.22, J3.23, J4.4, R11.1, R12.1
-12V: J3.10, J3.11, J3.14
/A0: RN1.9, U1.179, U12.38, U14.69
/A1: RN1.8, U1.2, U12.39, U14.66
/A2: RN1.6, U1.178, U9.1, U10.1, U12.41, U14.65, U17.1, U19.1
/A3: RN1.5, U1.3, U9.2, U10.2, U12.43, U14.64, U17.2, U19.2
/A4: RN1.4, U1.176, U9.3, U10.3, U12.44, U14.62, U17.3, U18.8, U19.3
/A5: RN1.3, U1.5, U9.4, U10.4, U12.45, U14.61, U17.4, U18.7, U19.4
/A6: RN1.2, U1.175, U9.5, U10.5, U12.46, U14.60, U17.5, U18.6, U19.5
/A7: RN1.7, U1.6, U9.18, U10.18, U12.47, U14.59, U17.18, U18.5, U19.18
/A8: RN2.5, U1.174, U9.19, U10.19, U14.58, U17.19, U18.27, U19.19
/A9: RN2.4, U1.7, U9.20, U10.20, U14.57, U17.20, U18.26, U19.20
/A10: RN2.3, U1.170, U9.21, U10.21, U14.56, U17.21, U18.23, U19.21
/A11: RN2.2, U1.11, U9.22, U10.22, U14.55, U17.22, U18.25, U19.22
/A12: RN2.6, U1.169, U9.23, U10.23, U14.54, U17.23, U18.4, U19.23
/A13: RN2.7, U1.12, U9.24, U10.24, U14.52, U17.24, U18.28, U19.24
/A14: RN2.8, U1.168, U9.25, U10.25, U14.50, U17.25, U18.29, U19.25
/A15: RN2.9, U1.13, U9.26, U10.26, U14.48, U17.26, U18.3, U19.26
/A16: RN3.9, U1.166, U9.27, U10.27, U14.47, U17.27, U18.2, U19.27
/A17: RN3.8, U1.15, U9.42, U10.42, U14.46, U17.42, U18.30, U19.42
/A18: RN3.7, U1.165, U9.43, U10.43, U14.45, U17.43, U18.1, U19.43
/A19: RN3.6, U1.16, U9.44, U10.44, U14.44, U17.44, U19.44
/A20: RN3.5, U1.164, U14.43
/A21: RN3.4, U1.17, U14.41
/A22: RN3.3, U1.160, U14.39
/A23: RN3.2, U1.21, U14.38
/A24: RN4.9, U1.159
/A25: RN4.8, U1.22
/A26: RN4.7, U1.158
/A27: RN4.6, U1.23
/A28: RN4.5, U1.151
/A29: RN4.4, U1.30
/A30: RN4.3, U1.144
/A31: RN4.2, U1.37
/BA0: U3.20, U4.20, U5.20, U6.20, U14.114
/BA1: U3.21, U4.21, U5.21, U6.21, U14.118
/CAS: U3.17, U4.17, U5.17, U6.17, U14.136
/DH0: U1.115, U8.2, U17.7, U23.47
/DH1: U1.114, U8.3, U17.8, U23.46
/DH2: U1.113, U8.5, U17.9, U23.44
/DH3: U1.110, U8.6, U17.10, U23.43
/DH4: U1.109, U8.8, U17.13, U23.41
/DH5: U1.108, U8.9, U17.14, U23.40
/DH6: U1.99, U8.11, U17.15, U23.38
/DH7: U1.98, U8.12, U17.16, U23.37
/DH8: U1.97, U8.13, U17.29, U23.36
/DH9: U1.94, U8.14, U17.30, U23.35
/DH10: U1.93, U8.16, U17.31, U23.33
/DH11: U1.92, U8.17, U17.32, U23.32
/DH12: U1.91, U8.19, U17.35, U23.30
/DH13: U1.90, U8.20, U17.36, U23.29
/DH14: U1.89, U8.22, U17.37, U23.27
/DH15: U1.87, U8.23, U17.38, U23.26
/DH16: U1.85, U11.2, U19.7, U24.26
/DH17: U1.84, U11.3, U19.8, U24.27
/DH18: U1.83, U11.5, U19.9, U24.29
/DH19: U1.82, U11.6, U19.10, U24.30
/DH20: U1.81, U11.8, U19.13, U24.32
/DH21: U1.80, U11.9, U19.14, U24.33
/DH22: U1.78, U11.11, U19.15, U24.35
/DH23: U1.76, U11.12, U19.16, U24.36
/DH24: U1.75, U11.13, U19.29, U24.47
/DH25: U1.74, U11.14, U19.30, U24.46
/DH26: U1.73, U11.16, U19.31, U24.44
/DH27: U1.72, U11.17, U19.32, U24.43
/DH28: U1.71, U11.19, U19.35, U24.41
/DH29: U1.68, U11.20, U19.36, U24.40
/DH30: U1.67, U11.22, U19.37, U24.38
/DH31: U1.66, U11.23, U19.38, U24.37
/DL0: U1.143, U2.2, U9.7, U15.36
/DL1: U1.141, U2.3, U9.8, U15.35
/DL2: U1.140, U2.5, U9.9, U15.33
/DL3: U1.139, U2.6, U9.10, U15.32
/DL4: U1.135, U2.8, U9.13, U15.30
/DL5: U1.134, U2.9, U9.14, U15.29
/DL6: U1.133, U2.11, U9.15, U15.27
/DL7: U1.131, U2.12, U9.16, U15.26
/DL8: U1.130, U2.13, U9.29, U15.37
/DL9: U1.129, U2.14, U9.30, U15.38
/DL10: U1.126, U2.16, U9.31, U15.40
/DL11: U1.125, U2.17, U9.32, U15.41
/DL12: U1.124, U2.19, U9.35, U15.43
/DL13: U1.123, U2.20, U9.36, U15.44
/DL14: U1.119, U2.22, U9.37, U15.46
/DL15: U1.118, U2.23, U9.38, U15.47
/DL16: U1.117, U7.2, U10.7, U16.47
/DL17: U1.107, U7.3, U10.8, U16.46
/DL18: U1.106, U7.5, U10.9, U16.44
/DL19: U1.105, U7.6, U10.10, U16.43
/DL20: U1.102, U7.8, U10.13, U16.41
/DL21: U1.101, U7.9, U10.14, U16.40
/DL22: U1.100, U7.11, U10.15, U16.38
/DL23: U1.51, U7.12, U10.16, U16.37
/DL24: U1.52, U7.13, U10.29, U16.36
/DL25: U1.55, U7.14, U10.30, U16.35
/DL26: U1.56, U7.16, U10.31, U16.33
/DL27: U1.57, U7.17, U10.32, U16.32
/DL28: U1.58, U7.19, U10.35, U16.30
/DL29: U1.62, U7.20, U10.36, U16.29
/DL30: U1.63, U7.22, U10.37, U16.27
/DL31: U1.64, U7.23, U10.38, U16.26
/D_A0: U3.23, U4.23, U5.23, U6.23, U14.120
/D_A1: U3.24, U4.24, U5.24, U6.24, U14.121
/D_A2: U3.25, U4.25, U5.25, U6.25, U14.122
/D_A3: U3.26, U4.26, U5.26, U6.26, U14.123
/D_A4: U3.29, U4.29, U5.29, U6.29, U14.126
/D_A5: U3.30, U4.30, U5.30, U6.30, U14.124
/D_A6: U3.31, U4.31, U5.31, U6.31, U14.129
/D_A7: U3.32, U4.32, U5.32, U6.32, U14.127
/D_A8: U3.33, U4.33, U5.33, U6.33, U14.130
/D_A9: U3.34, U4.34, U5.34, U6.34, U14.131
/D_A10: U3.22, U4.22, U5.22, U6.22, U14.119
/D_A11: U3.35, U4.35, U5.35, U6.35, U14.134
/D_A12: U3.36, U4.36, U5.36, U6.36, U14.135
/D_CKE: U3.37, U4.37, U5.37, U6.37, U14.141
/D_CLK: U3.38, U4.38, U5.38, U6.38, U14.140
/D_CS: U3.19, U4.19, U5.19, U6.19, U14.132
/D_D0: U3.2, U15.13
/D_D1: U3.4, U15.14
/D_D2: U3.5, U15.16
/D_D3: U3.7, U15.17
/D_D4: U3.8, U15.19
/D_D5: U3.10, U15.20
/D_D6: U3.11, U15.22
/D_D7: U3.13, U15.23
/D_D8: U3.42, U15.12
/D_D9: U3.44, U15.11
/D_D10: U3.45, U15.9
/D_D11: U3.47, U15.8
/D_D12: U3.48, U15.6
/D_D13: U3.50, U15.5
/D_D14: U3.51, U15.3
/D_D15: U3.53, U15.2
/D_D16: U5.2, U16.2
/D_D17: U5.4, U16.3
/D_D18: U5.5, U16.5
/D_D19: U5.7, U16.6
/D_D20: U5.8, U16.8
/D_D21: U5.10, U16.9
/D_D22: U5.11, U16.11
/D_D23: U5.13, U16.12
/D_D24: U5.42, U16.13
/D_D25: U5.44, U16.14
/D_D26: U5.45, U16.16
/D_D27: U5.47, U16.17
/D_D28: U5.48, U16.19
/D_D29: U5.50, U16.20
/D_D30: U5.51, U16.22
/D_D31: U5.53, U16.23
/D_D32: U4.2, U23.2
/D_D33: U4.4, U23.3
/D_D34: U4.5, U23.5
/D_D35: U4.7, U23.6
/D_D36: U4.8, U23.8
/D_D37: U4.10, U23.9
/D_D38: U4.11, U23.11
/D_D39: U4.13, U23.12
/D_D40: U4.42, U23.13
/D_D41: U4.44, U23.14
/D_D42: U4.45, U23.16
/D_D43: U4.47, U23.17
/D_D44: U4.48, U23.19
/D_D45: U4.50, U23.20
/D_D46: U4.51, U23.22
/D_D47: U4.53, U23.23
/D_D48: U6.2, U24.23
/D_D49: U6.4, U24.22
/D_D50: U6.5, U24.20
/D_D51: U6.7, U24.19
/D_D52: U6.8, U24.17
/D_D53: U6.10, U24.16
/D_D54: U6.11, U24.14
/D_D55: U6.13, U24.13
/D_D56: U6.42, U24.2
/D_D57: U6.44, U24.3
/D_D58: U6.45, U24.5
/D_D59: U6.47, U24.6
/D_D60: U6.48, U24.8
/D_D61: U6.50, U24.9
/D_D62: U6.51, U24.11
/D_D63: U6.53, U24.12
/D_WE: U3.16, U4.16, U5.16, U6.16, U14.138
/ID0: U2.36, U2.47, U7.36, U7.47, U8.36, U8.47, U11.36, U11.47, U12.25, U18.13
/ID1: U2.35, U2.46, U7.35, U7.46, U8.35, U8.46, U11.35, U11.46, U12.26, U18.14
/ID2: U2.33, U2.44, U7.33, U7.44, U8.33, U8.44, U11.33, U11.44, U12.27, U18.15
/ID3: U2.32, U2.43, U7.32, U7.43, U8.32, U8.43, U11.32, U11.43, U12.28, U18.17
/ID4: U2.30, U2.41, U7.30, U7.41, U8.30, U8.41, U11.30, U11.41, U12.29, U18.18
/ID5: U2.29, U2.40, U7.29, U7.40, U8.29, U8.40, U11.29, U11.40, U12.30, U18.19
/ID6: U2.27, U2.38, U7.27, U7.38, U8.27, U8.38, U11.27, U11.38, U12.32, U18.20
/ID7: U2.26, U2.37, U7.26, U7.37, U8.26, U8.37, U11.26, U11.37, U12.33, U18.21
/RAS: U3.18, U4.18, U5.18, U6.18, U14.113
/RXI+: J1.7, R8.2, U13.26
/RXI-: J1.8, R7.1, U13.27
/TXO+: J1.1, R9.2, U13.30
/TXO-: J1.2, R24.1, U13.31
AP0: RN5.2, U1.231, U12.75
AP1: RN5.3, U1.230, U12.77
AP2: RN5.4, U1.227, U12.74
AP3: RN5.5, U1.226, U12.76
APE: R16.2, U1.218, U12.79
CS_ROM: U12.141, U18.22
CS_SRAM_0: U9.6, U12.131
CS_SRAM_1: U10.6, U12.132
CS_SRAM_2: U12.134, U17.6
CS_SRAM_3: U12.135, U19.6
DPE: R21.2, U1.217, U12.78
DQM0: U3.15, U9.40, U14.101
DQM1: U3.39, U9.39, U14.100
DQM2: U5.15, U10.40, U14.102
DQM3: U5.39, U10.39, U14.105
DQM4: U4.15, U14.106, U17.40
DQM5: U4.39, U14.110, U17.39
DQM6: U6.15, U14.111, U19.40
DQM7: U6.39, U14.112, U19.39
GBL: RN6.4, U1.1
GND: C1.1, C1.2, C1.3, C1.4, C2.1, C2.2, C2.3, C2.4, C3.1, C3.2, C3.3, C3.4, C4.1, C4.2, C4.3, C4.4, C5.1, C5.2, C5.3, C5.4, C6.1, C6.2, C6.3, C6.4, C7.1, C7.2, C7.3, C7.4, C8.1, C9.1, C9.2, C9.3, C9.4, C10.1, C10.2, C10.3, C10.4, C11.1, C11.2, C11.3, C11.4, C12.1, C12.2, C12.3, C12.4, C13.1, C13.2, C13.3, C13.4, C14.2, C15.2, C16.2, C17.2, C18.2, C19.2, C20.2, C21.2, C31.2, C32.2, C33.2, J1.4, J1.5, J2.2, J2.19, J2.22, J2.24, J2.26, J2.28, J2.30, J2.40, J3.3, J3.5, J3.7, J3.15, J3.17, J3.18, J3.19, J3.24, J4.3, JP1.1, JP2.1, JP3.1, JP4.1, P1.4, P1.6, P1.8, P1.10, P1.11, P1.12, P1.14, P1.16, P1.18, P1.20, R4.1, R5.1, R6.1, R10.2, R25.1, SW1.3, U1.8, U1.9, U1.18, U1.19, U1.29, U1.33, U1.39, U1.43, U1.49, U1.53, U1.60, U1.65, U1.69, U1.77, U1.86, U1.95, U1.103, U1.111, U1.116, U1.120, U1.127, U1.132, U1.136, U1.142, U1.146, U1.152, U1.161, U1.162, U1.171, U1.172, U1.181, U1.182, U1.193, U1.206, U1.220, U1.228, U1.238, U1.239, U2.4, U2.10, U2.15, U2.21, U2.28, U2.34, U2.39, U2.45, U3.6, U3.12, U3.28, U3.41, U3.46, U3.52, U3.54, U4.6, U4.12, U4.28, U4.41, U4.46, U4.52, U4.54, U5.6, U5.12, U5.28, U5.41, U5.46, U5.52, U5.54, U6.6, U6.12, U6.28, U6.41, U6.46, U6.52, U6.54, U7.4, U7.10, U7.15, U7.21, U7.28, U7.34, U7.39, U7.45, U8.4, U8.10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
HRESET: P1.3, U1.214
INT: U1.188, U12.110
JT_CHAIN0: U1.198, U12.19
JT_CHAIN1: U12.20, U14.19
JT_CHAIN2: P1.13, U14.20
JT_TCK: P1.9, U1.201, U12.18, U14.18
JT_TDI: P1.5, U1.199
JT_TMS: P1.7, U1.200, U12.16, U14.16
unnamed: C8.2, C14.1, R22.2, U1.209
unnamed: C15.1, U13.2, Y1.1
unnamed: C16.1, U13.3, Y1.2
unnamed: C20.1, R7.2, R8.1
unnamed: C21.1, J1.3, L1.1, R9.1, R24.2
unnamed: D1.1, R10.1
unnamed: J1.9, U13.14
unnamed: J1.10, R6.2
unnamed: J1.11, U13.15
unnamed: J1.12, R5.2
unnamed: J2.31, R25.2
unnamed: J3.9, SW1.1
unnamed: J3.16, SW1.2
unnamed: J4.1, R14.2
unnamed: J4.5, R13.2
unnamed: JP1.2, R23.2, U1.211
unnamed: JP2.2, R1.2, U1.213
unnamed: JP3.2, R2.2, U1.210
unnamed: JP4.2, R3.2, U1.208
unnamed: R4.2, U13.16
unnamed: R11.2, R14.1, U12.89
unnamed: R12.2, R13.1, U12.88
unnamed: R15.2, U1.145
unnamed: R17.2, U1.149
unnamed: R18.2, U1.32
unnamed: R19.2, U1.36
unnamed: R20.2, U1.216
READ: U9.41, U10.41, U12.120, U17.41, U18.24, U19.41
SD_DDIR: U14.32, U15.1, U15.24, U16.1, U16.24, U23.1, U23.24, U24.1, U24.24
SD_DOE: U14.33, U15.25, U15.48, U16.25, U16.48, U23.25, U23.48, U24.25, U24.48
SRESET: P1.15, U1.189
SYSCLK: U1.212, Y2.3
TBST: RN5.9, U1.192
TLBISYNC: U1.233, U12.111
TSIZ0: RN5.6, U1.197, U12.81
TSIZ1: RN5.7, U1.196, U12.80
TSIZ2: RN5.8, U1.195, U12.85
TT0: RN6.6, U1.191, U12.101
TT1: RN6.7, U1.190, U12.100
TT2: RN6.8, U1.185, U12.102
TT3: RN6.9, U1.184, U12.105
TT4: RN6.2, U1.180, U12.106
WRITE: U9.17, U10.17, U12.121, U17.17, U18.31, U19.17

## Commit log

2019-07-20 added readme
2019-07-20 updated schematic
2019-07-20 Routed a bit of the new SRAM stuff
